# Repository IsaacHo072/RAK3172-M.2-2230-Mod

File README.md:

# RAK3172-M.2-2230-Mod
M.2 Custom Module PCB for RAK3172 LoRa Radio

This PCB route the UART, I2C, SPI signals of the RAK3172 LoRa Radio to a M.2 E-key connector, in 2230 form factor.
The connector pinout is compatible with the Sparkfun M.2 "MicroMod Function Board", but without any GPIO pins provided.

It provides a onboard DC-DC supply, capable of 3.3-5.5V input, to provide power to the RAK3172. 

A EEPROM is also connected to the I2C lines. 

The board can be programmed using a Tag-Connect TC2030-IDC-NL programming cable, with a SWD programmer.

The board can be tested with a computer using the USB UART converter board.

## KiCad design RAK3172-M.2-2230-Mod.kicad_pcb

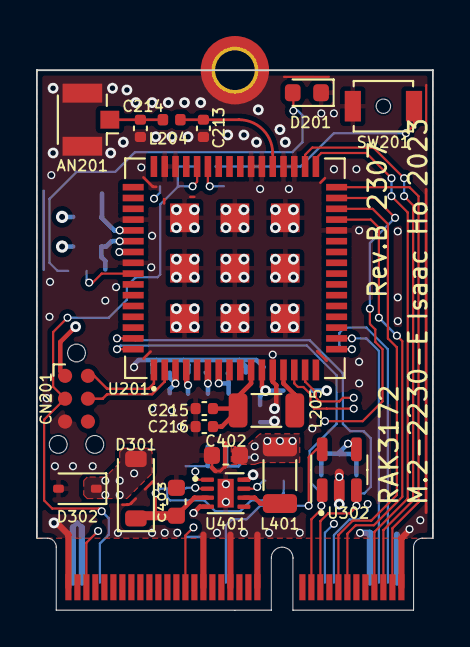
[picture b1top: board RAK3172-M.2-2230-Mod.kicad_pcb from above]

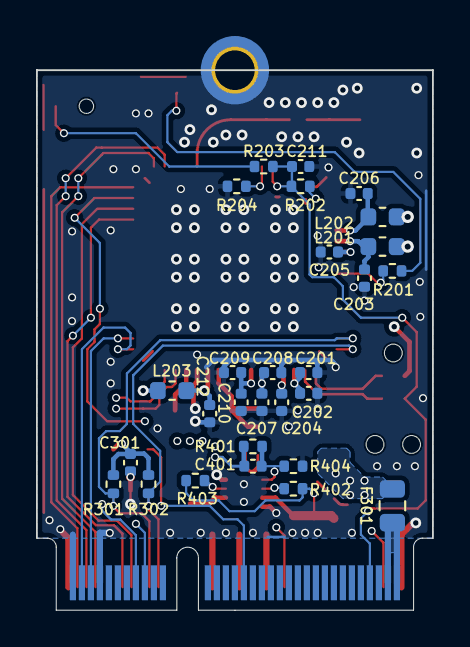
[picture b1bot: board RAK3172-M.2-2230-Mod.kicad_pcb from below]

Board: 4 copper layers, 22.0 x 30.0 mm, 48 parts (28 on the bottom side), 36 nets.

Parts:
AN201: Conn_Coaxial; U.FL_Hirose_U.FL-R-SMT-1_Vertical
C201, C207: 4.7uF; C_0402_1005Metric
C202, C205, C208, C210, C211, C212, C216, C301: 100nF; C_0402_1005Metric
C203, C204, C206, C209: 1uF; C_0402_1005Metric
C213, C214: DNF; C_0402_1005Metric
C215: 470nF; C_0402_1005Metric
C401: 10pF; C_0402_1005Metric
C402: 22uF; C_0603_1608Metric
C403: 10uF; C_0603_1608Metric
CN201: Conn_ARM_SWD_TagConnect_TC2030-NL; Tag-Connect_TC2030-IDC-NL_2x03_P1.27mm_Vertical
D201: LED; LED_0603_1608Metric
D301: D_Schottky; D_SOD-123
D302: 5V; D_SOD-323
F301: 0.5A; Fuse_0805_2012Metric
H301: MountingHole_Pad; MountingHole_2.2mm_M2_DIN965_Pad_TopBottom
J301: Conn_02x38_Odd_Even; NGFF_E
L201, L202, L203: 120; L_0603_1608Metric
L204: 0R; L_0402_1005Metric
L205: 15uH; L_1206_3216Metric
L401: 1uH; L_1206_3216Metric
R201, R301, R302: 3.3k; R_0402_1005Metric
R202, R204: 10k; R_0402_1005Metric
R203: 1k; R_0402_1005Metric
R401, R402, R403: 100k; R_0402_1005Metric
R404: 22.1k; R_0402_1005Metric
SW201: SW_SPST; SW_SPST_B3U-1000P-B
U201: RAK3172-SIP; LGA-73_12x12mm_P0.6mm
U302: 24LC01; SOT-23-5
U401: SY8883DFC; DFN-8-1EP_2x2mm_P0.5mm_EP0.9x1.6mm

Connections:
3.3V: C201.1, C202.1, C204.1, C205.1, C207.1, C208.1, C209.1, C210.1, C301.1, C401.1, C402.1, CN201.1 (VCC), L201.2, L202.2, L203.1, L401.2, R202.2, R301.1, R302.1, R401.1, U201.3 (VDD), U201.4 (VBAT), U201.6 (VREF+), U201.7 (VDDA), U201.55 (VDD), U302.4 (VCC)
+5V: C403.1, D301.1 (K), R402.1, R403.1, U401.3 (IN)
/M.2 E-Key Connector/EEPROM_WP: J301.40, U302.5 (WP)
/M.2 E-Key Connector/V_{CC}Fused: D301.2 (A), D302.1 (A1), F301.2
/Power Supply/3.3VPG: R402.2, U401.2 (PG)
/RAK3172/BOOT0: R204.1, U201.43 (BOOT_0)
/RAK3172/PA13/SWDIO: CN201.2 (SWDIO), U201.1 (PA13)
/RAK3172/PA14/SWCLK: CN201.4 (SWCLK), U201.2 (PA14)
/RAK3172/PB1: R201.1, U201.57 (PB1)
/RAK3172/RF_OUT: C213.1, L204.1, U201.37 (RF_OUT)
/RAK3172/RF_OUT_CONN: AN201.1 (In), C214.1, L204.2
/RAK3172/VDDPA: C206.1, L202.1, U201.53 (VDDPA)
/RAK3172/VDDRF: C203.1, L201.1, U201.54 (VDDRF)
/RAK3172/VDDSMPS: C212.1, L203.2, U201.11 (VDDMPS)
/RAK3172/VFBSMPS: C215.1, C216.1, L205.1, U201.10 (VFBSMPS)
/RAK3172/VLXSMPS: L205.2, U201.13 (VLXSMPS)
CTS: J301.18, U201.15 (PB4)
DFU_FC_RX: J301.6, U201.18 (PB7/UART1_RX)
DFU_FC_TX: J301.4, U201.17 (PB6/UART1_TX)
DFU_~RST: C211.1, CN201.3 (~RESET), J301.68, R202.1, R203.2, U201.44 (NRST)
F1/~CS: J301.49, U201.31 (PA4)
GND: AN201.2 (Ext), C201.2, C202.2, C203.2, C204.2, C205.2, C206.2, C207.2, C208.2, C209.2, C210.2, C211.2, C212.2, C213.2, C214.2, C215.2, C216.2, C301.2, C402.2, C403.2, CN201.5 (GND), D201.1 (K), D302.2 (A2), H301.1, J301.1, J301.2, J301.8, J301.33, J301.39, J301.45, J301.75, R204.2, R404.2, SW201.1 (A), U201.12 (GND), U201.28 (GND), U201.35 (GND), U201.36 (GND), U201.38 (GND), U201.39 (GND), U201.46 (GND), U201.47 (GND), U201.52 (GND), U201.56 (GND), U201.65 (GND), U201.66 (GND), U201.67 (GND), U201.68 (GND), U201.69 (GND), U201.70 (GND), U201.71 (GND), U201.72 (GND), U201.73 (GND), U302.2 (VSS), U401.4 (PGND), U401.8 (AGND), U401.9 (PGND)
I2C_SCL: J301.21, R302.2, U201.64 (PA12), U302.1 (SCL)
I2C_SDA: J301.19, R301.2, U201.63 (PA11), U302.3 (SDA)
unnamed: D201.2 (A), R201.2
unnamed: R203.1, SW201.2 (B)
unnamed: C401.2, R401.2, R404.1, U401.1 (FB)
unnamed: L401.1, U401.6 (LX)
PWR_EN: J301.71, R403.2, U401.7 (EN)
RTS: J301.16, U201.14 (PB3)
RX: J301.15, U201.30 (PA3/UART2_RX)
SPI_SCK: J301.3, U201.32 (PA5)
SPI_SDI: J301.5, U201.34 (PA7)
SPI_SDO: J301.7, U201.33 (PA6)
TX: J301.13, U201.29 (PA2/UART2_TX)
VCC: F301.1, J301.72, J301.74

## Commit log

2023-02-25 Updated 3D model of 1206 inductor to 1210
2023-03-02 Moved files in panel folder
2023-03-02 Added submodule
2023-03-02 Updated path
2023-03-02 Removed old files
2023-03-02 Moved board pdf
2023-03-04 Added board photo
2023-06-12 Update RAK3172-MOD-USB
